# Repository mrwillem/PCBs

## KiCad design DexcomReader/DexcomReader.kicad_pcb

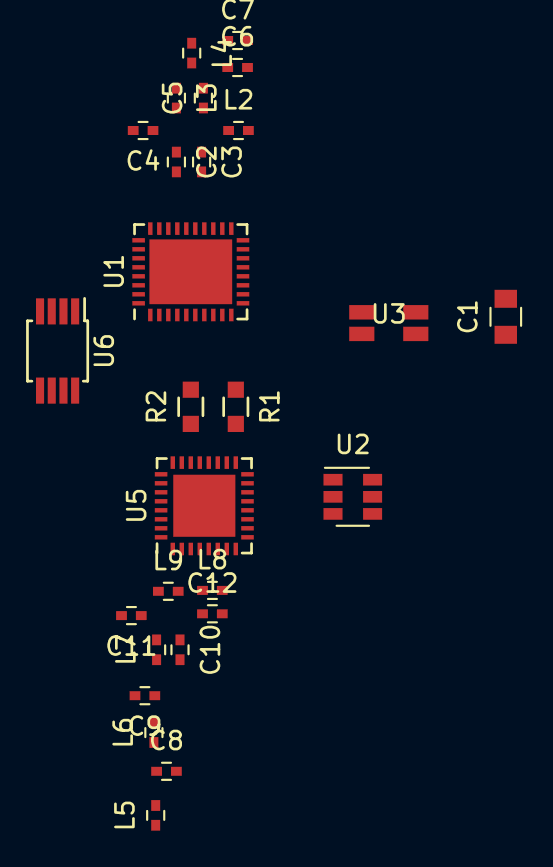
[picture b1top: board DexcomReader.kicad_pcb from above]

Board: 2 copper layers, 28 parts (1 on the bottom side), 21 nets, no tracks yet.

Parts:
C1: 100nF; C_0805
C2, C3: 100pF; C_0402
C4, C5, C8, C9, C10, C11: 1pF; C_0402
C6: 1,8pF; C_0402
C7: 1,5pF; C_0402
C12: 6,8pF; C_0402
L2, L3: 1,2nH; C_0402
L4, L5, L6: 1,2 nH; C_0402
L7: 2,7nH; C_0402
L8: 2,4nH; C_0402
L9: 6,2nH; C_0402
R1, R2: R; R_0603_HandSolder
U1: CC2511F32; QFN-36-1EP_5x6mm_Pitch0.5mm
U2: BQ21040; SOT-23-6
U3: USB-CMC-Wuerth; CMC-SMD-Wuerth
U4: TVS-ARRAY-SOT5; SOT-23-5
U5: CC2640_32PIN; QFN-32-1EP_5x5mm_Pitch0.5mm
U6: MB85RS16N; MSOP-8_3x3mm_Pitch0.65mm

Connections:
+3V3: C1.2, U6.3, U6.7, U6.8
GNDD: C1.1, C4.2, C6.2, C7.2, C8.2, C9.2, C11.2, C12.2, L2.2, R1.2, U4.2, U6.4
MEMCS: U1.35, U6.1
MISO: U1.32, U6.2
MOSI: U1.33, U6.5
unnamed: C7.1, L4.1
unnamed: C2.1, C4.1, L3.2
unnamed: C2.2, U1.24
unnamed: C3.1, C5.1, L2.1
unnamed: C3.2, U1.23
unnamed: C5.2, C6.1, L3.1, L4.2
unnamed: C8.1, L5.2, L6.1
unnamed: C10.1, L8.1, L9.2, U5.2
unnamed: C9.1, C10.2, L6.2, L7.1
unnamed: C11.1, L7.2, L9.1, U5.1
unnamed: C12.1, L8.2, U5.3
unnamed: R1.1, R2.2, U1.6
unnamed: U2.6, U4.5
SCK: U1.34, U6.6
USBDM: U1.11, U3.2, U4.4
USBDP: U1.10, U3.3, U4.3

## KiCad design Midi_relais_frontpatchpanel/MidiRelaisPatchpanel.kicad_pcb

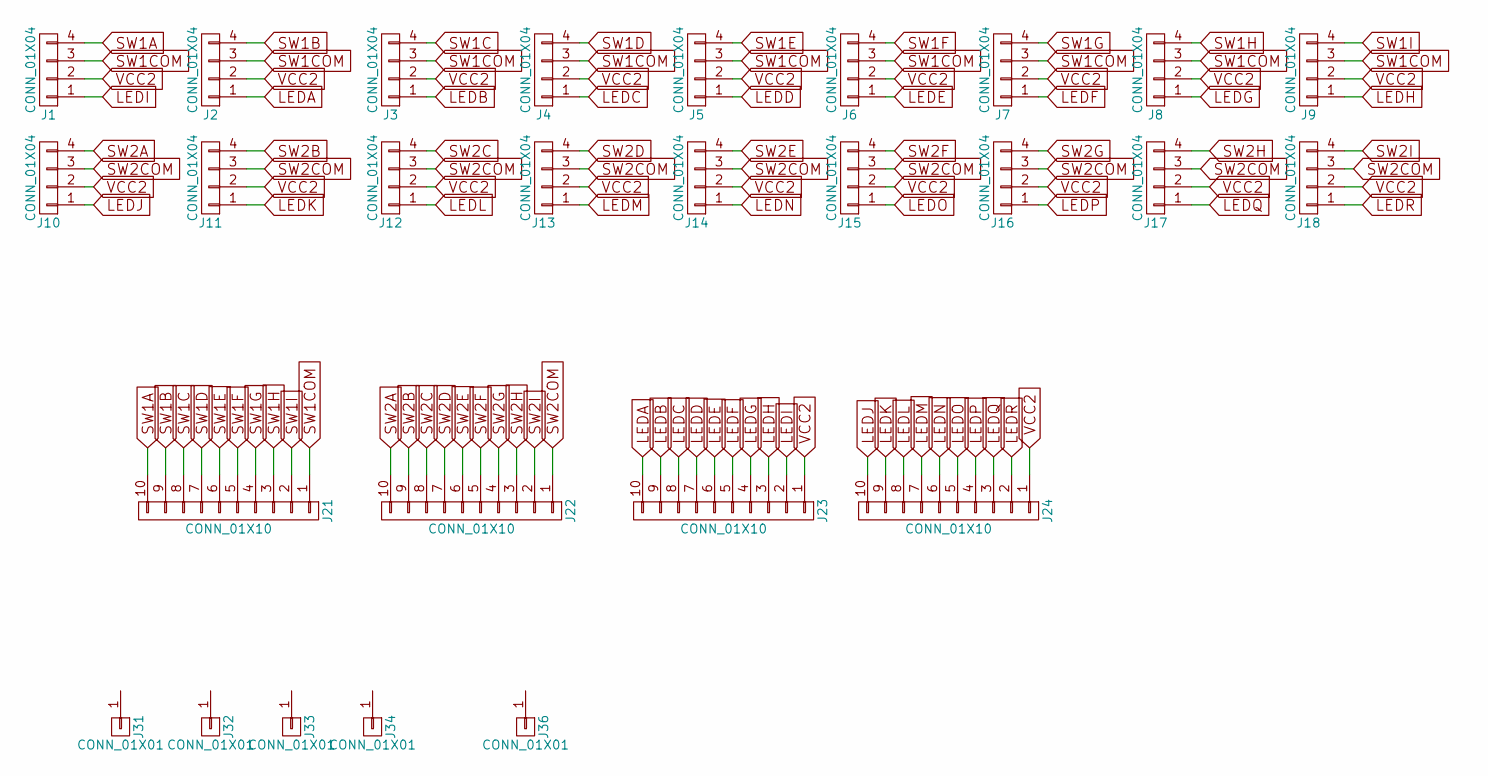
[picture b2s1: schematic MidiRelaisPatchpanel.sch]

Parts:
J1, J2, J3, J4, J5, J6, J7, J8, J9, J10, J11, J12, J13, J14, J15, J16, J17, J18: CONN_01X04; JST_ZH_1.5mm_01x04
J21, J22, J23, J24: CONN_01X10; PINHEAD1-10
J31, J32, J33, J34, J36: CONN_01X01; MountingHole_3.2mm_M3

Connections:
LEDA: J2.1, J23.10
LEDB: J3.1, J23.9
LEDC: J4.1, J23.8
LEDD: J5.1, J23.7
LEDE: J6.1, J23.6
LEDF: J7.1, J23.5
LEDG: J8.1, J23.4
LEDH: J9.1, J23.3
LEDI: J1.1, J23.2
LEDJ: J10.1, J24.10
LEDK: J11.1, J24.9
LEDL: J12.1, J24.8
LEDM: J13.1, J24.7
LEDN: J14.1, J24.6
LEDO: J15.1, J24.5
LEDP: J16.1, J24.4
LEDQ: J17.1, J24.3
LEDR: J18.1, J24.2
SW1A: J1.4, J21.10
SW1B: J2.4, J21.9
SW1C: J3.4, J21.8
SW1COM: J1.3, J2.3, J3.3, J4.3, J5.3, J6.3, J7.3, J8.3, J9.3, J21.1
SW1D: J4.4, J21.7
SW1E: J5.4, J21.6
SW1F: J6.4, J21.5
SW1G: J7.4, J21.4
SW1H: J8.4, J21.3
SW1I: J9.4, J21.2
SW2A: J10.4, J22.10
SW2B: J11.4, J22.9
SW2C: J12.4, J22.8
SW2COM: J10.3, J11.3, J12.3, J13.3, J14.3, J15.3, J16.3, J17.3, J18.3, J22.1
SW2D: J13.4, J22.7
SW2E: J14.4, J22.6
SW2F: J15.4, J22.5
SW2G: J16.4, J22.4
SW2H: J17.4, J22.3
SW2I: J18.4, J22.2
VCC2: J1.2, J2.2, J3.2, J4.2, J5.2, J6.2, J7.2, J8.2, J9.2, J10.2, J11.2, J12.2, J13.2, J14.2, J15.2, J16.2, J17.2, J18.2, J23.1, J24.1

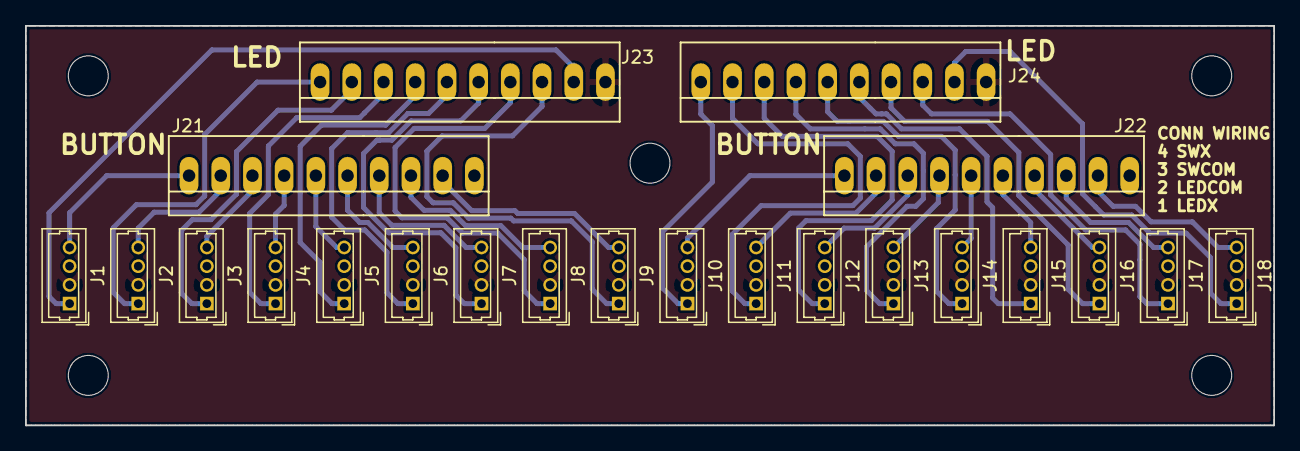
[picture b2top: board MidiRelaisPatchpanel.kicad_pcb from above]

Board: 2 copper layers, 100.0 x 32.0 mm, 27 parts (0 on the bottom side), 39 nets.

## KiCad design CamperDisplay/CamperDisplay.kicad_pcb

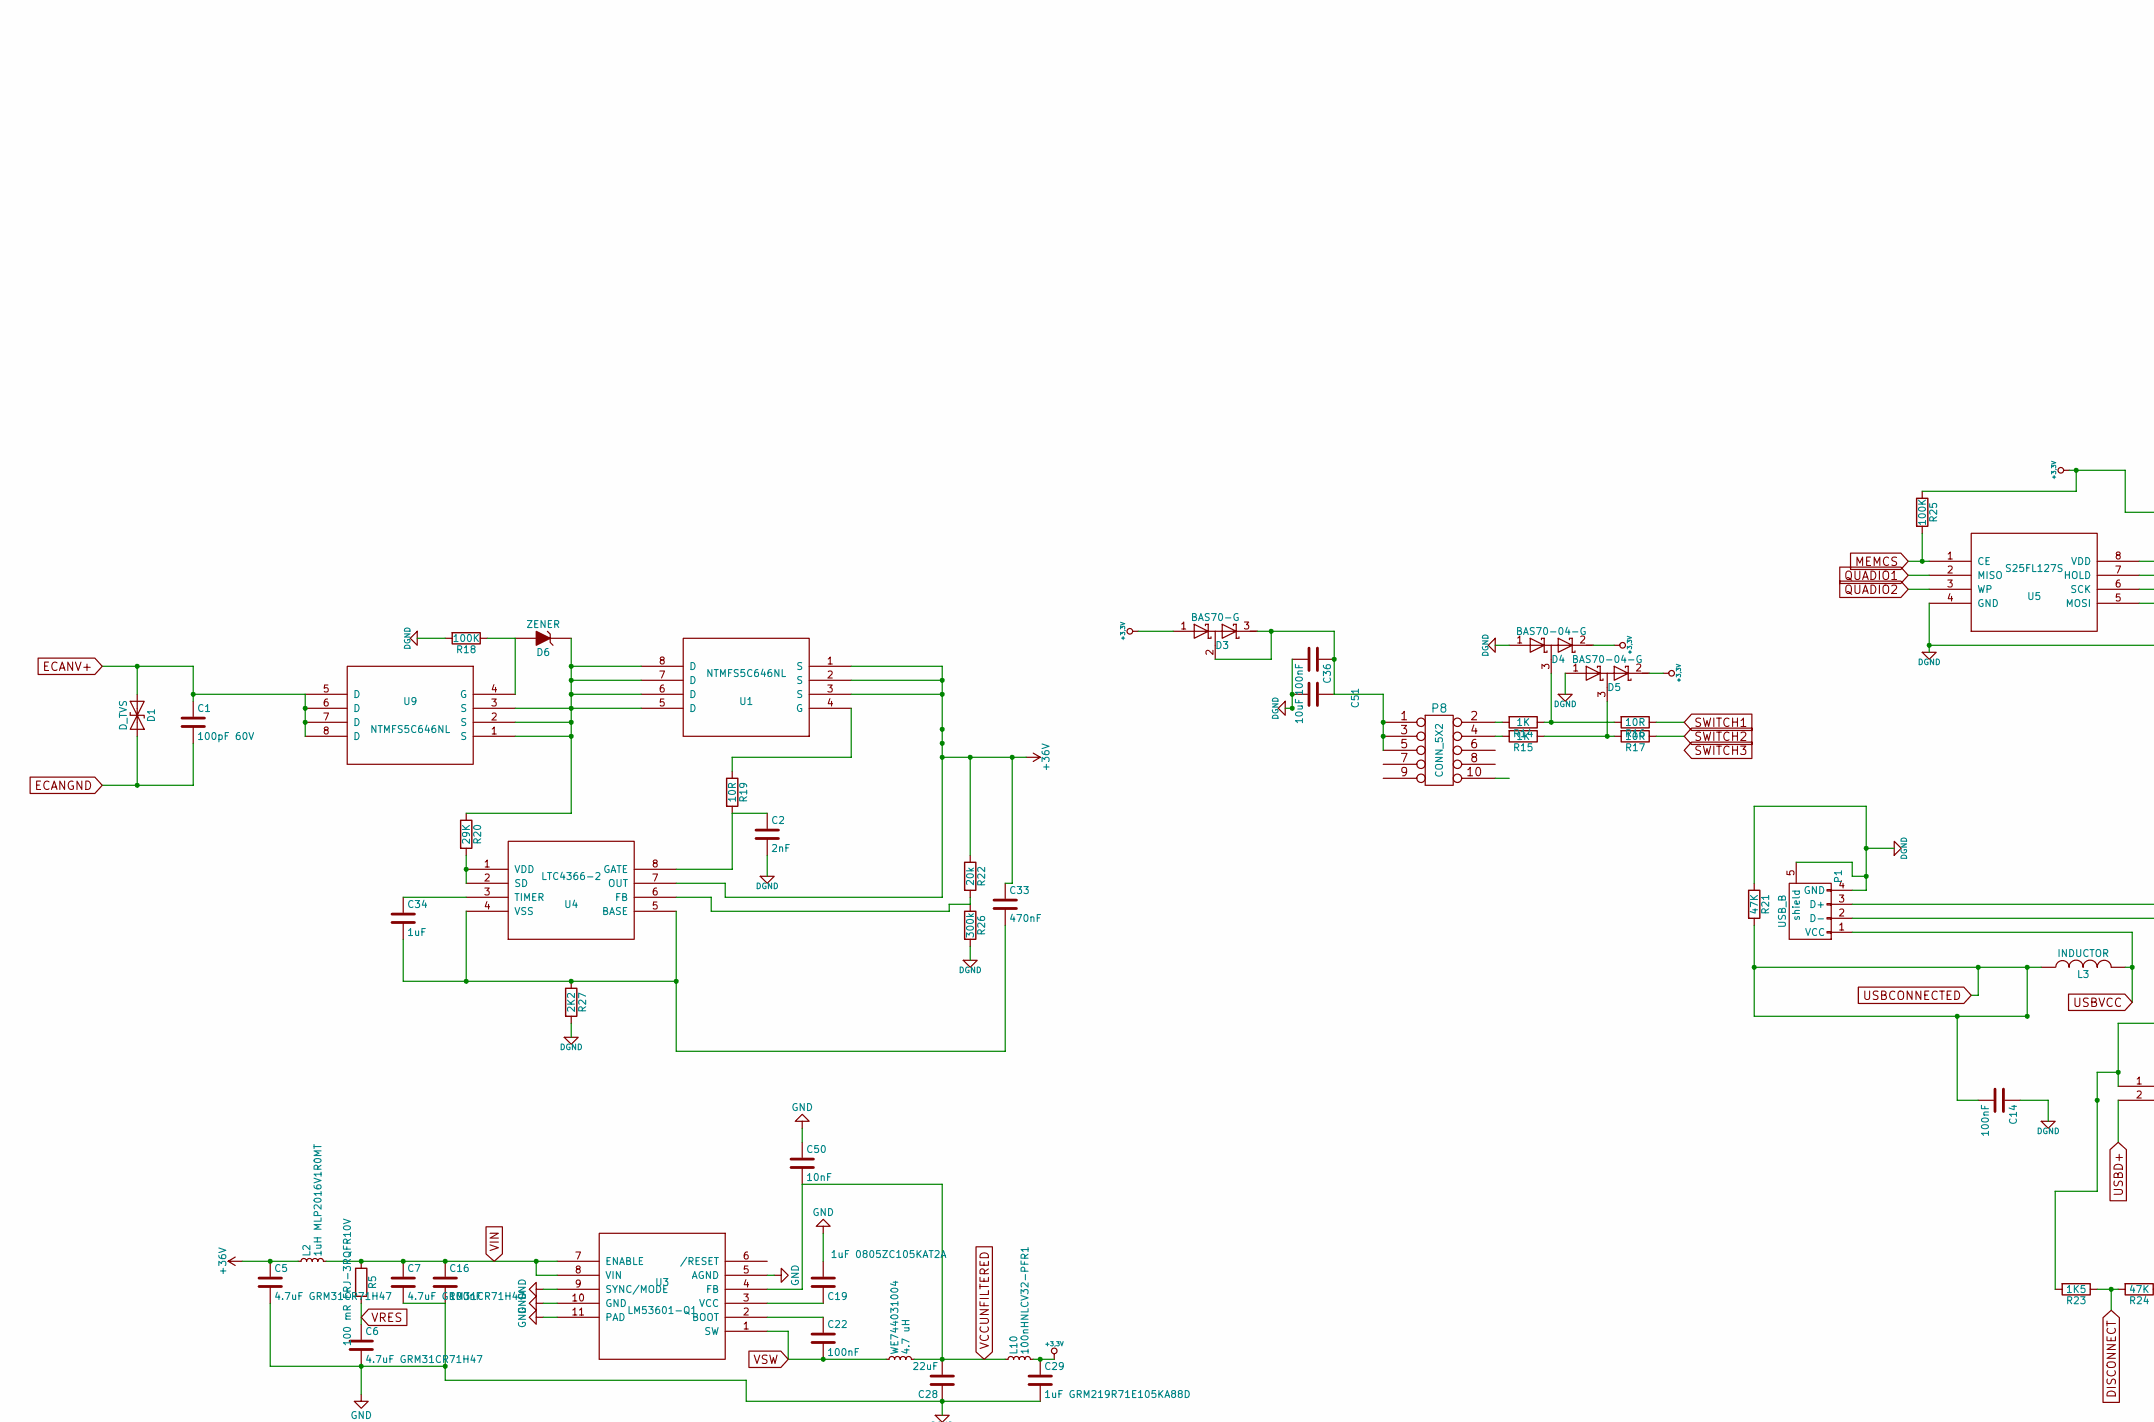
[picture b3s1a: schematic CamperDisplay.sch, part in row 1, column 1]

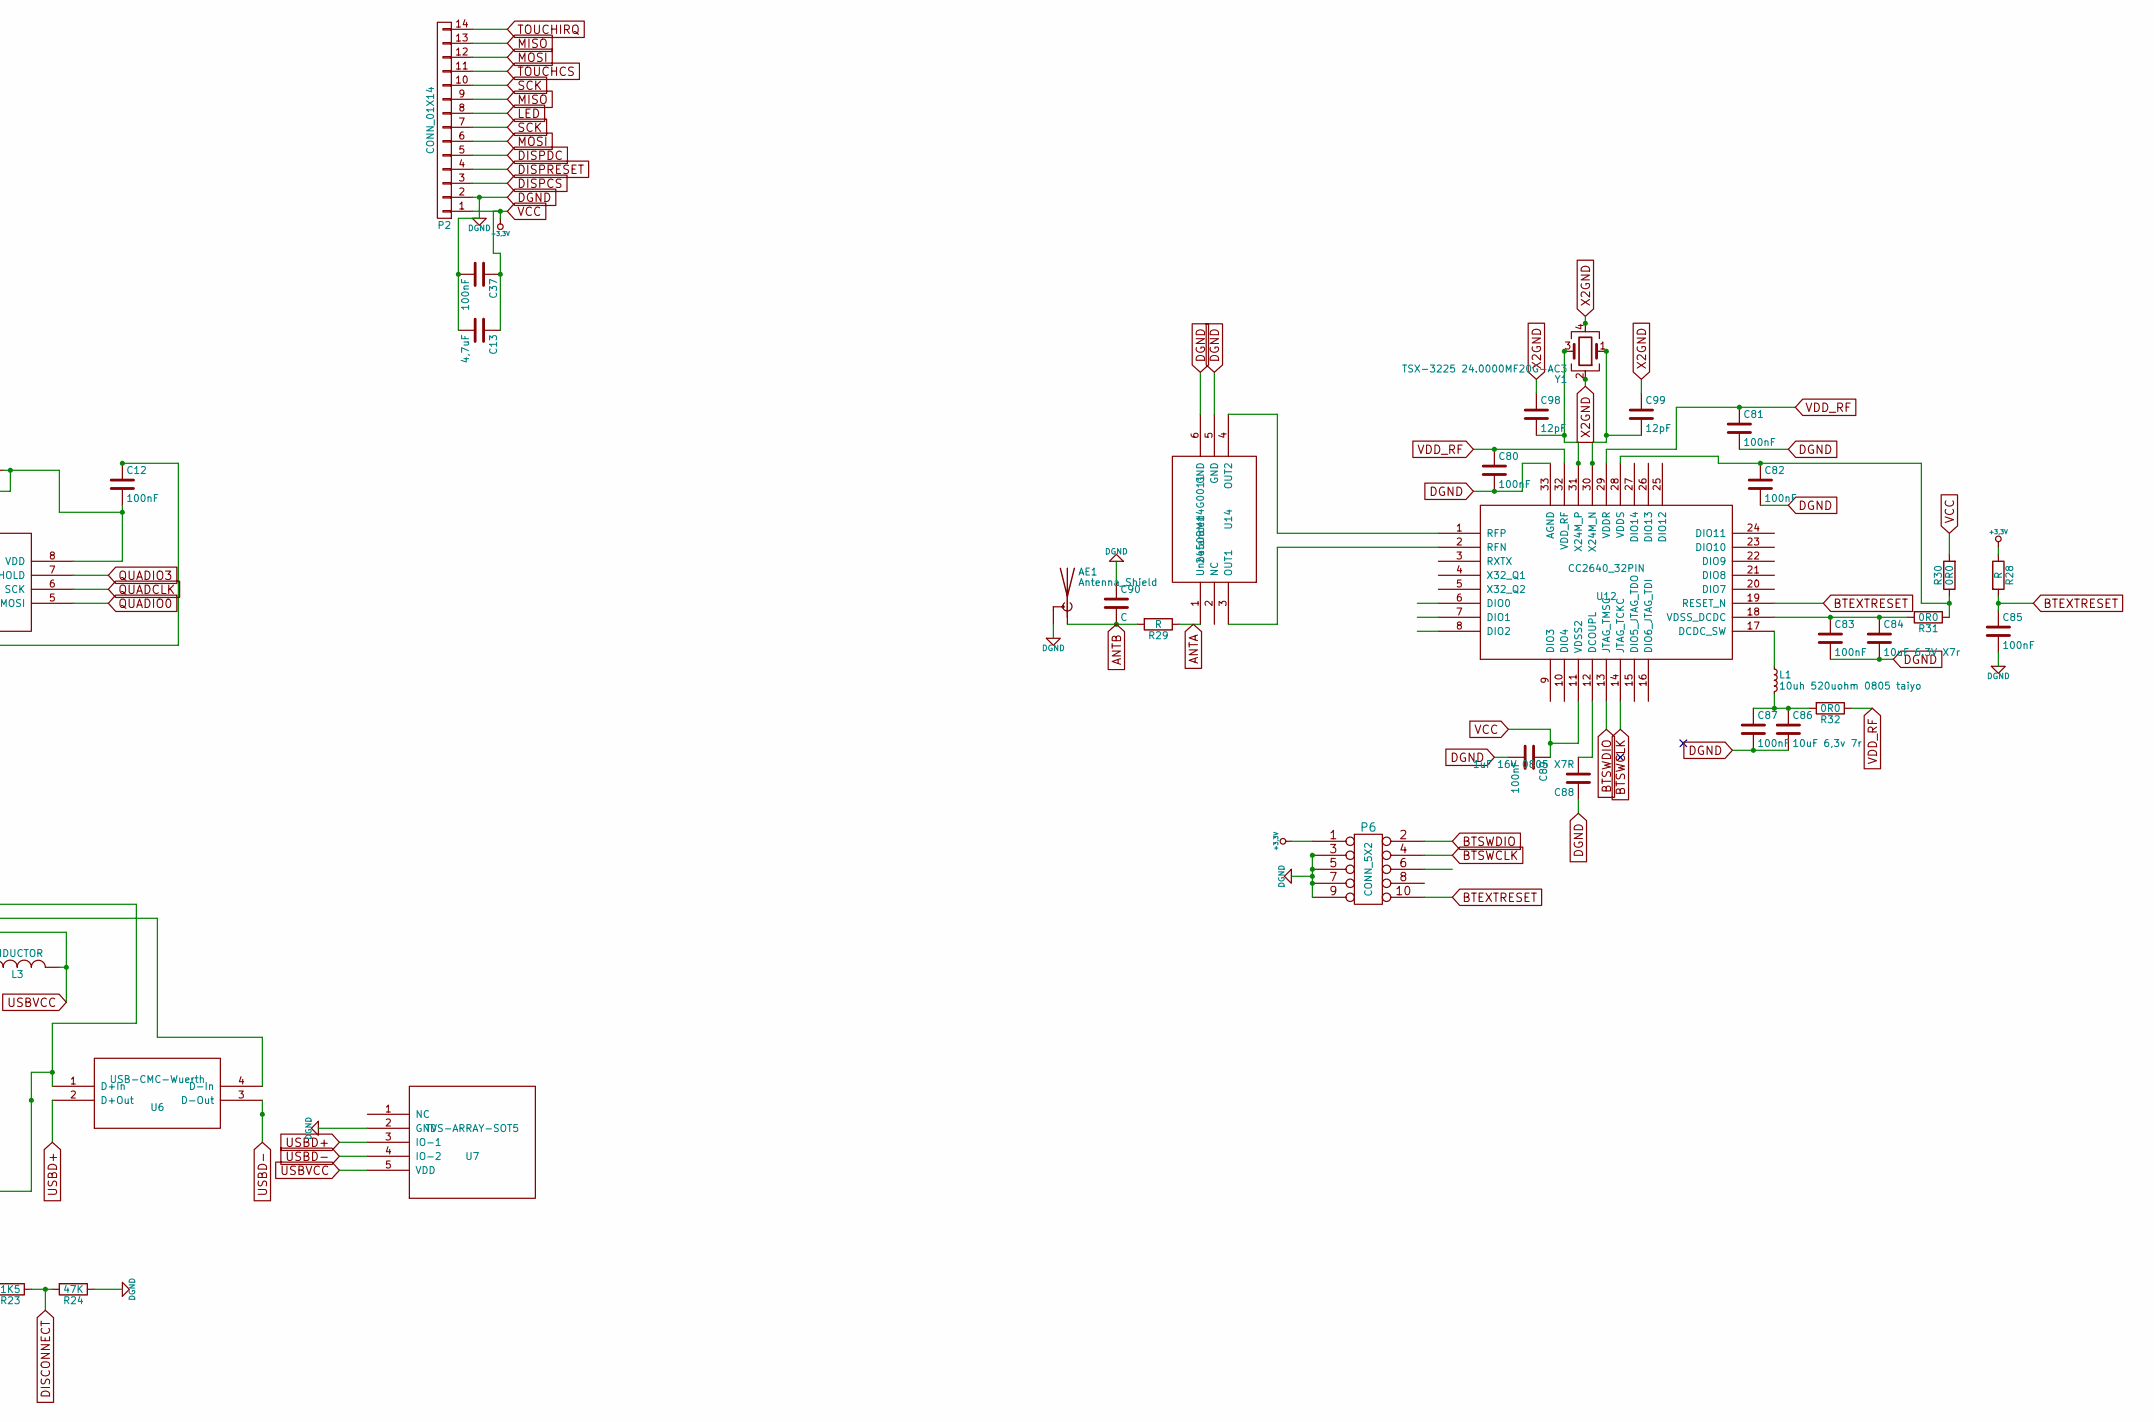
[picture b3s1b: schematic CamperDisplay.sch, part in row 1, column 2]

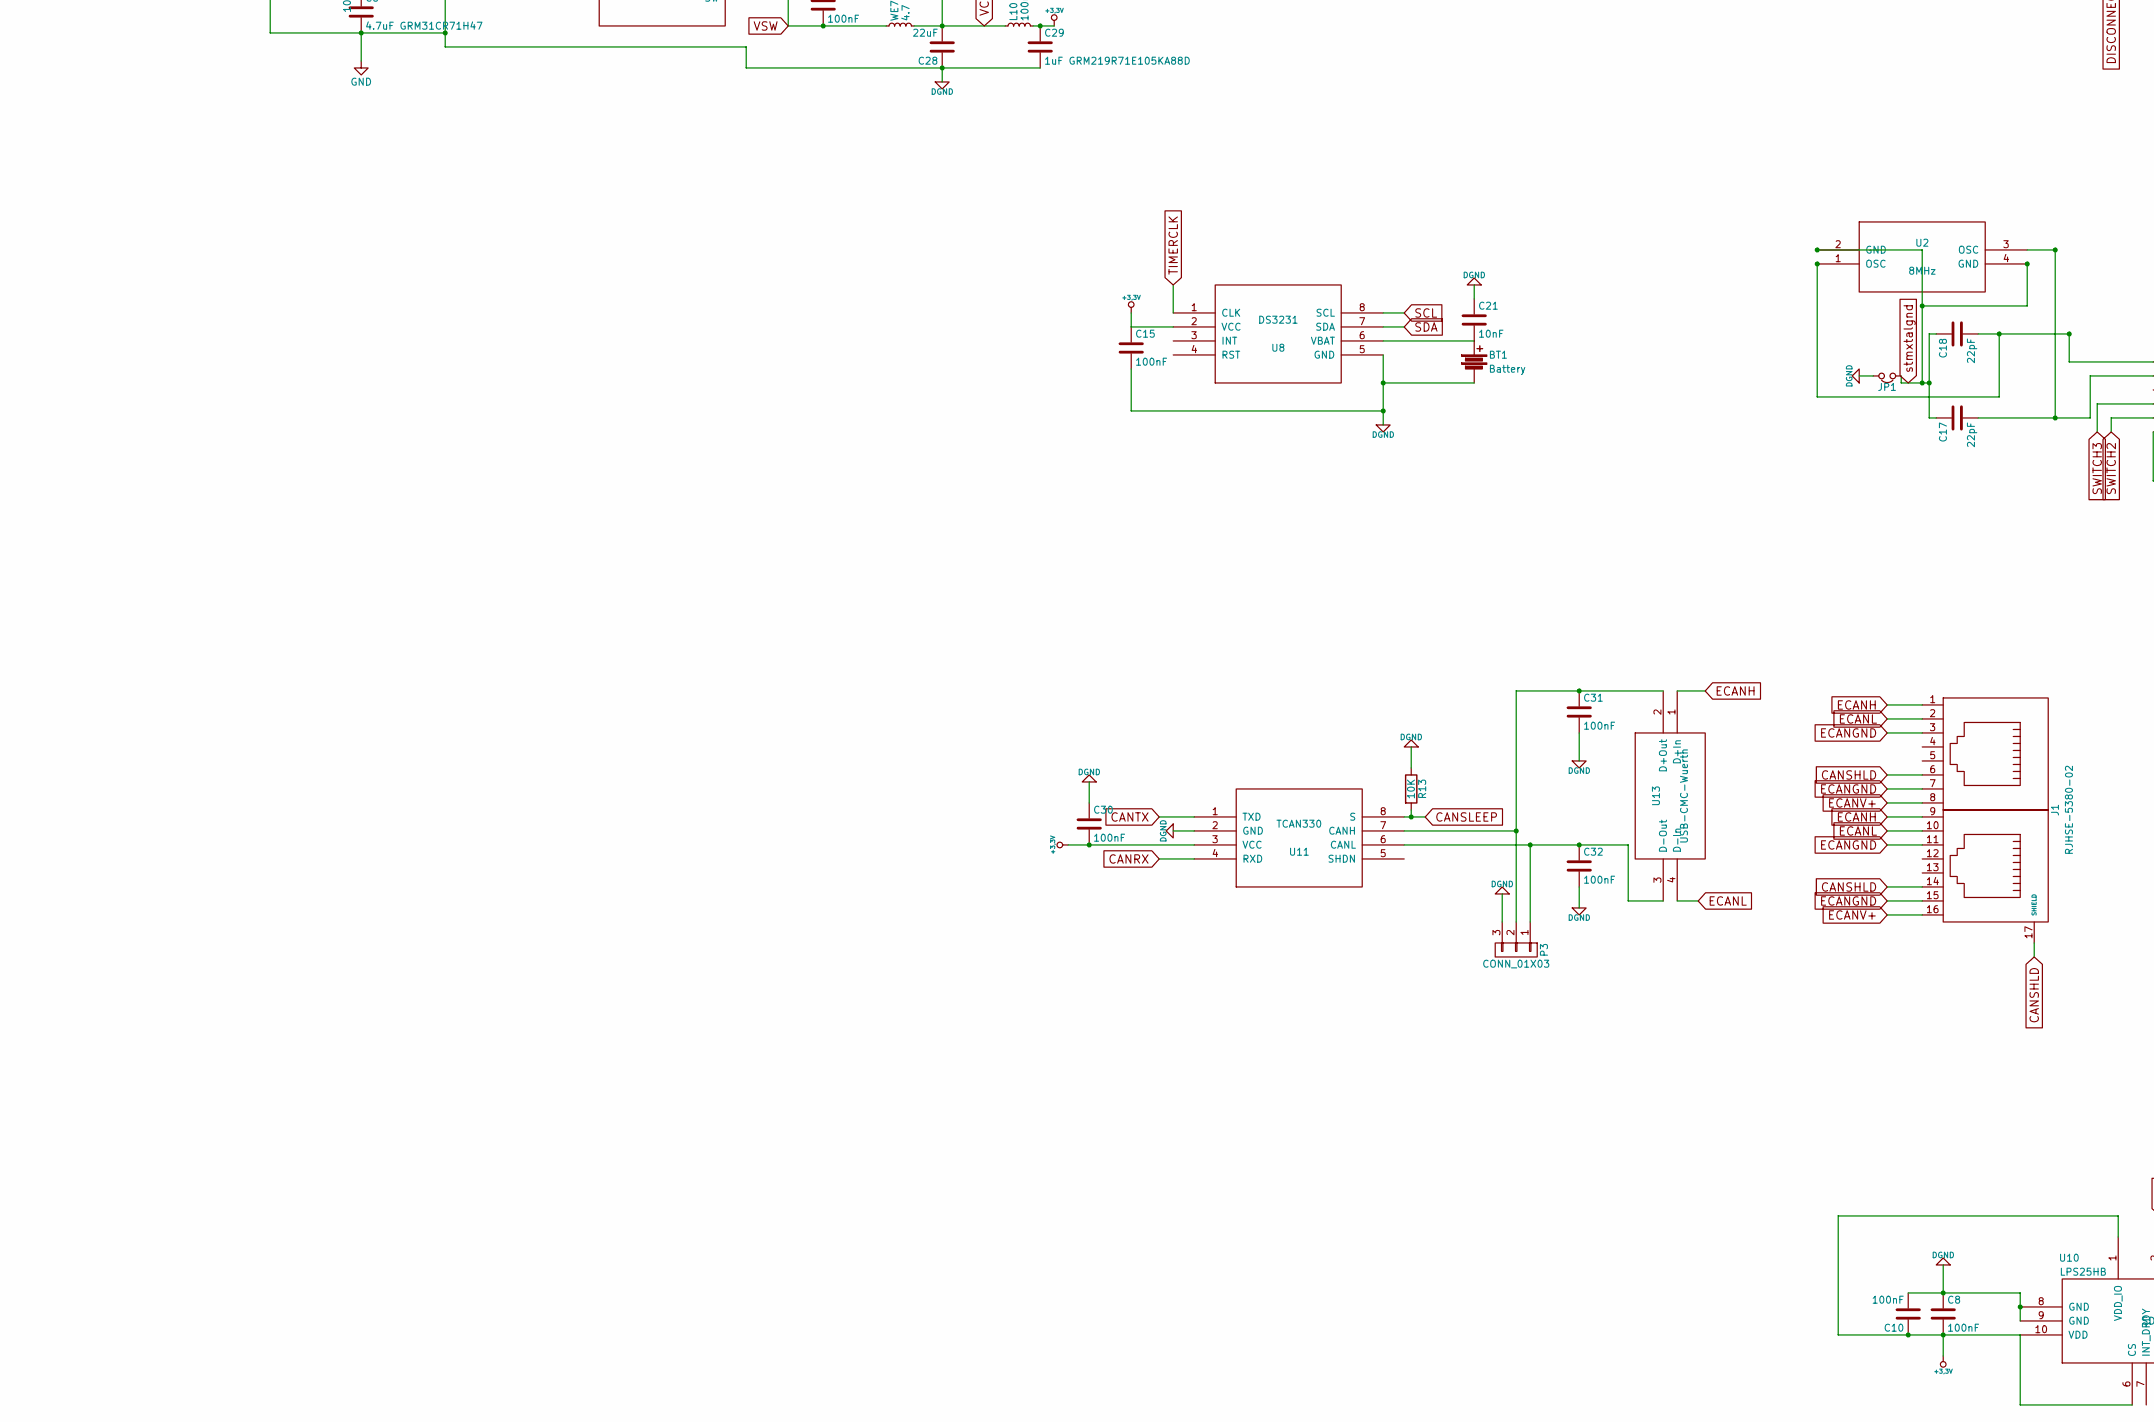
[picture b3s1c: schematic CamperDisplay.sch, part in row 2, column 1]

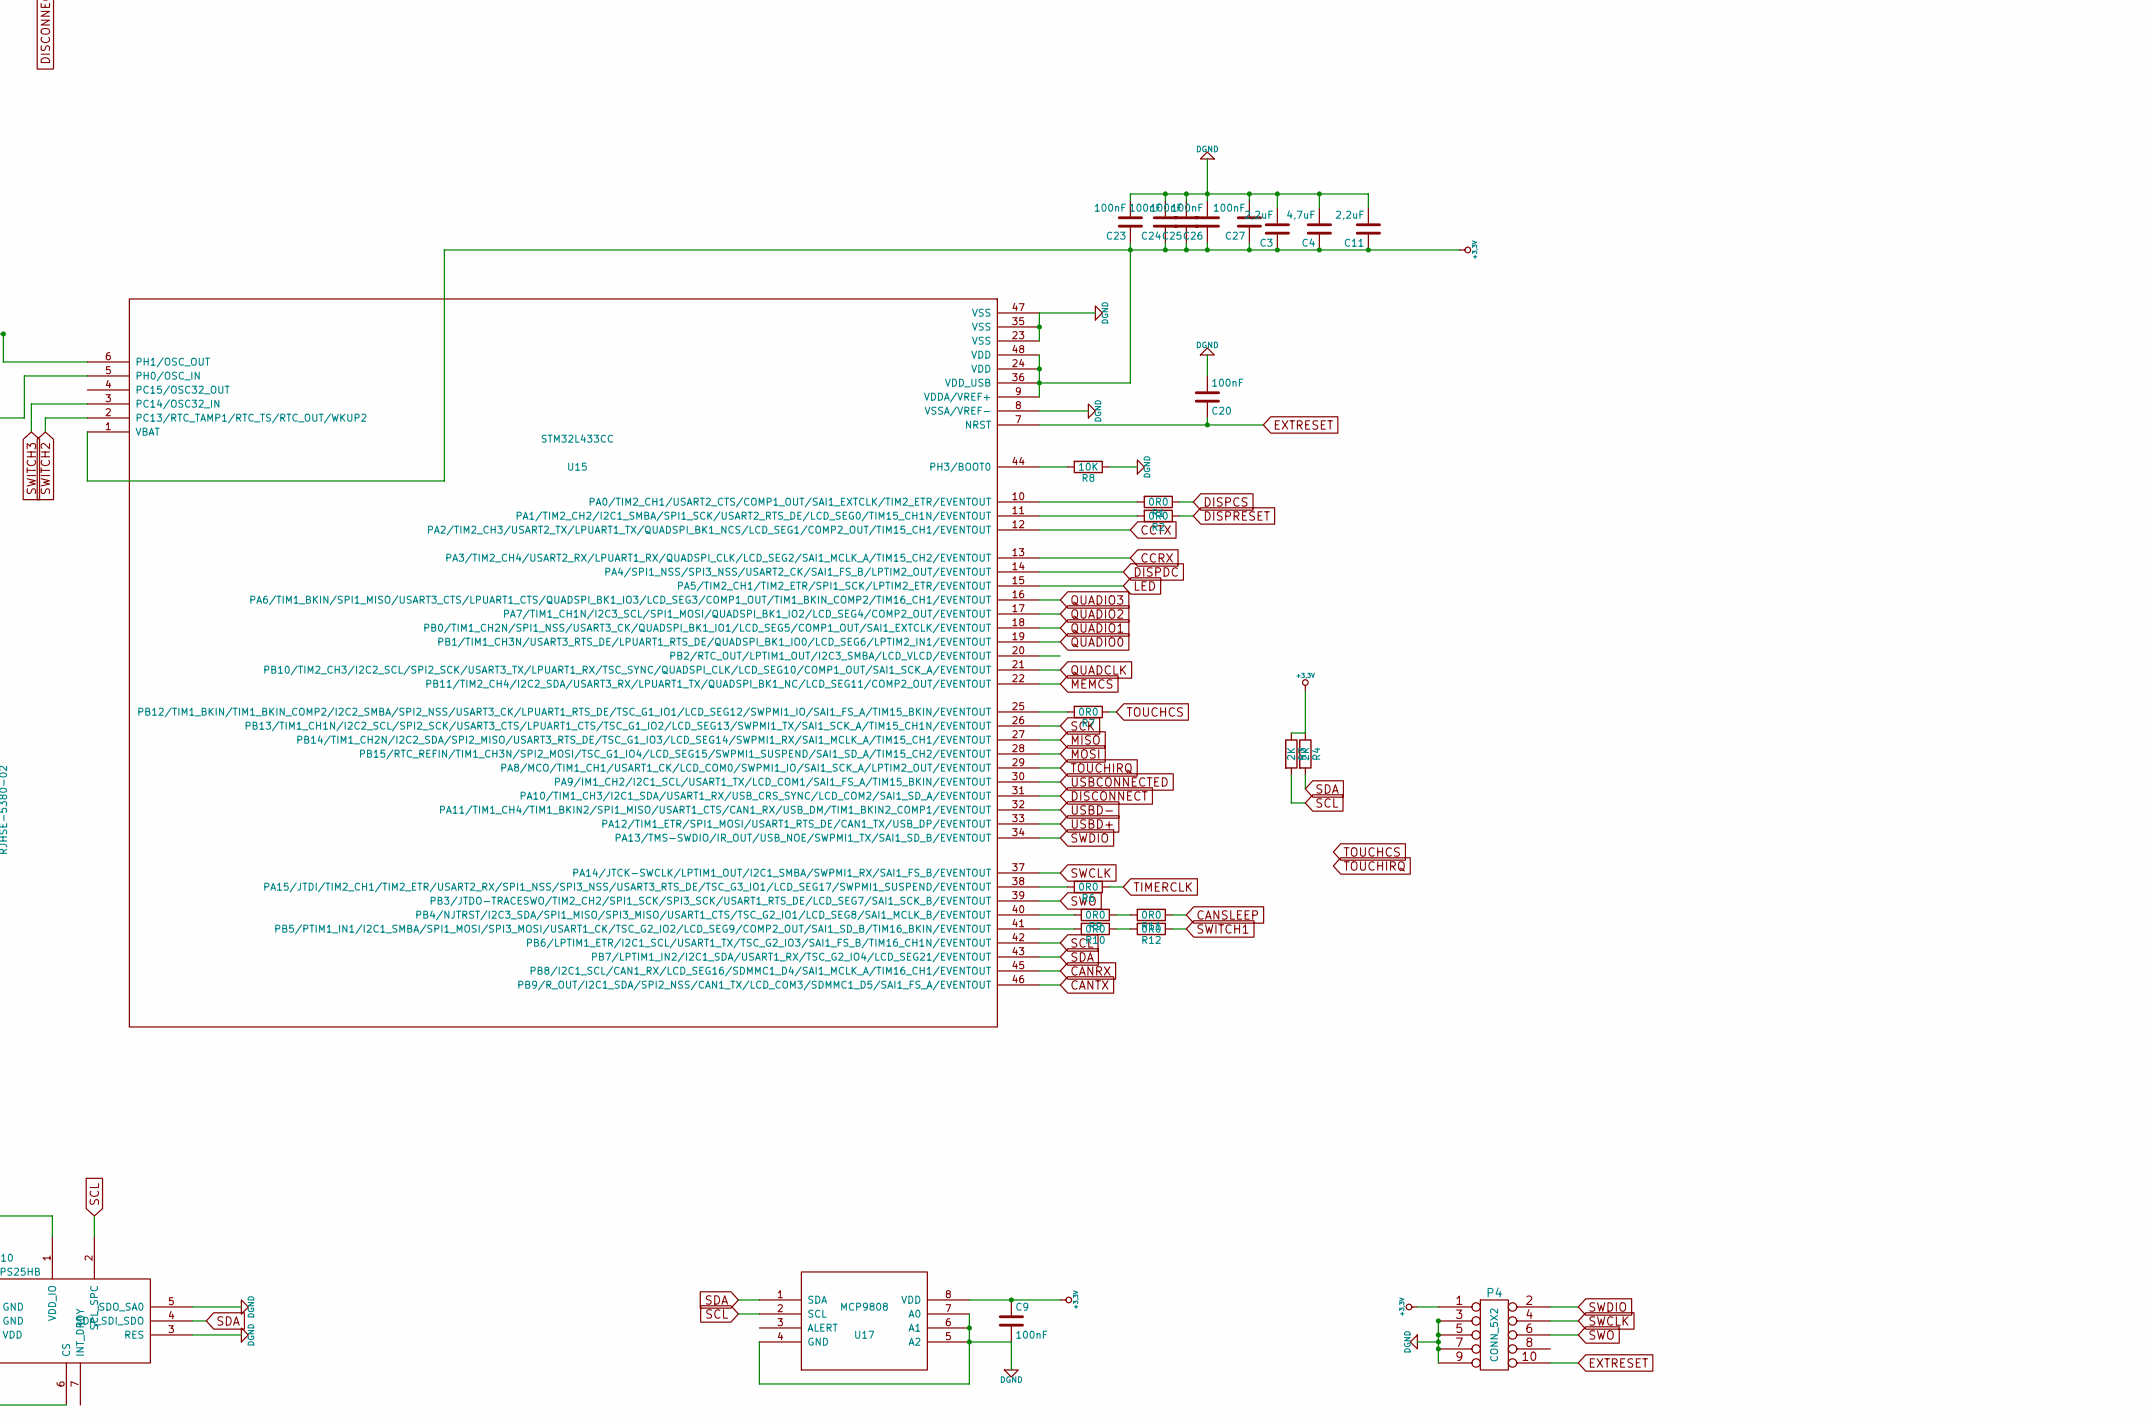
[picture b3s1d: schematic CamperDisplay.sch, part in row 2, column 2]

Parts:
AE1: Antenna_Shield; Molex_2.4GhZ_Chip_Antenna_146175
BT1: Battery; BatterieHolderCR1025_SMD
C1: 100pF 60V; C_0805
C2: 2nF; C_0805
C3: 2,2uF; C_0805
C4, C13: 4,7uF; C_1206
C5, C6, C7: 4.7uF GRM31CR71H47; C_1206
C8, C9, C10, C12, C14, C15, C16, C20, C22, C23, C24, C25, C26, C27, C30, C31, C32, C36, C37: 100nF; C_0805
C11: 2,2uF; C_1206
C17, C18: 22pF; C_0805
C19: 1uF 0805ZC105KAT2A; C_0805
C21, C50: 10nF; C_0805
C28: 22uF; C_1210
C29: 1uF GRM219R71E105KA88D; C_0805
C33: 470nF; C_0805
C34: 1uF; C_0805
C51: 10uF; C_1206
C80, C81, C82, C83, C85, C87, C89: 100nF; C_0603
C84: 10uF 6.3V X7r; C_0603
C86: 10uF 6,3v 7r; C_0603
C88: 1uF 16V 0805 X7R; C_0603
C90: C; C_0402
C98, C99: 12pF; C_0603
D1: D_TVS; D_SMB_Standard
D3: BAS70-G; SOT-23
D4, D5: BAS70-04-G; SOT-23
D6: ZENER; D_SOD-323_HandSoldering
J1: RJHSE-5380-02; RJHSE538X-02-noled
JP1: Jumper_NC_Small; NetTie-I_Connected_SMD
L1: 10uh 520uohm 0805 taiyo
L2: 1uH MLP2016V1R0MT; Choke_SMD_2016_Standard
L3: INDUCTOR; C_0805_HandSoldering
L10: 100nHNLCV32-PFR1; Choke_SMD_3225_Standard
P1: USB_B; USB_Mini-B
P2: CONN_01X14; 2.4inchQVGASPIwithTouch
P3: CONN_01X03; SOT-23
P4, P6: CONN_5X2; Pin_Header_Straight_2x05_Pitch1.27mm
P8: CONN_5X2; weidmueller_8
R1, R2, R7: 0R0; R_1206
R3, R4: 2K; R_0805_HandSolder
R5: 100 mR ERJ-3RQFR10V; R_0805
R6, R9, R10, R11, R12, R30, R31, R32: 0R0; R_0805_HandSolder
R8, R13: 10K; R_0805_HandSolder
R14, R15: 1K; R_0805_HandSolder
R16, R17, R19: 10R; R_0805_HandSolder
R18, R25: 100K; R_0805_HandSolder
R20: 29K; R_0805_HandSolder
R21, R24: 47K; R_0603_HandSolder
R22: 20k; R_0805_HandSolder
R23: 1K5; R_0603_HandSolder
R26: 300k; R_0805_HandSolder
R27: 2K2; R_0805_HandSolder
R28: R; R_0805_HandSolder
R29: R; R_0402
U1, U9: NTMFS5C646NL; PowerPack1212-8S_Pitch0.65mm
U2: 8MHz; Crystal_SMD_EuroQuartz_MT-4pin_3.2x2.5mm_hand
U3: LM53601-Q1; VSON10_Thermal_Pad
U4: LTC4366-2; SOT23-8
U5: S25FL127S; SOIJ-8_5.3x5.3mm_Pitch1.27mm
U6, U13: USB-CMC-Wuerth; CMC-SMD-Wuerth
U7: TVS-ARRAY-SOT5; SOT-23-5
U8: DS3231; SOIC-8_3.9x4.9mm_Pitch1.27mm
U10: LPS25HB; HLGA-10_2x2mm_Pitch0.5mm
U11: TCAN330; SOIC-8_3.9x4.9mm_Pitch1.27mm
U12: CC2640_32PIN; QFN-32-1EP_5x5mm_Pitch0.5mm_HandSolder
U14: 2450BM14G0011
U15: STM32L433CC; LQFP-48_7x7mm_Pitch0.5mm
U17: MCP9808; MSOP-8_3x3mm_Pitch0.65mm
WE744031004: 4.7 uH; Choke_SMD_4.3x4.3_H3
Y1: TSX-3225 24.0000MF20G-AC3; Crystal_SMD_EuroQuartz_MT-4pin_3.2x2.5mm_hand

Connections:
+36V: C5.1, C33.1, L2.1, R22.1, U1.1 (S), U1.2 (S), U1.3 (S), U4.7 (OUT)
ANTA: R29.1, U14.1 (Unbalanced)
ANTB: AE1.1 (A), C90.2, R29.2
BTEXTRESET: C85.1, P6.10, R28.2, U12.19 (RESET_N)
BTSWCLK: P6.4, U12.14 (JTAG_TCKC)
BTSWDIO: P6.2, U12.13 (JTAG_TMSC)
CANRX: U11.4 (RXD), U15.45 (PB8/I2C1_SCL/CAN1_RX/LCD_SEG16/SDMMC1_D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)
CANSHLD: J1.6, J1.14, J1.17 (SHIELD)
CANSLEEP: R11.1, R13.2, U11.8 (S)
CANTX: U11.1 (TXD), U15.46 (PB9/R_OUT/I2C1_SDA/SPI2_NSS/CAN1_TX/LCD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)
DGND: AE1.2 (Shield), BT1.2, C2.2, C3.2, C4.2, C5.2, C6.2, C7.2, C8.1, C9.2, C10.2, C11.2, C12.1, C13.2, C14.1, C15.2, C16.2, C19.2, C20.2, C21.1, C23.2, C24.2, C25.2, C26.2, C27.2, C28.1, C29.2, C30.1, C31.2, C32.2, C36.2, C37.2, C50.1, C51.2, C80.2, C81.2, C82.2, C83.2, C84.2, C85.2, C86.2, C87.2, C88.1, C89.2, C90.1, D4.1 (A), D5.1 (A), JP1.1, P1.4 (GND), P1.5 (shield), P2.2, P3.3, P4.3, P4.5, P4.7, P4.9, P6.3, P6.5, P6.7, P6.9, R8.1, R13.1, R18.2, R21.1, R24.1, R26.2, R27.2, U3.5 (AGND), U3.9 (SYNC/MODE), U3.10 (GND), U3.11 (PAD), U5.4 (GND), U7.2 (GND), U8.5 (GND), U10.3 (RES), U10.5 (SDO_SA0), U10.8 (GND), U10.9 (GND), U11.2 (GND), U12.33 (AGND), U14.5 (GND), U14.6 (GND), U15.8 (VSSA/VREF-), U15.23 (VSS), U15.35 (VSS), U15.47 (VSS), U17.4 (GND), U17.5 (A2), U17.6 (A1), U17.7 (A0)
DISCONNECT: R23.1, R24.2, U15.31 (PA10/TIM1_CH3/I2C1_SDA/USART1_RX/USB_CR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)
DISPCS: P2.3, R1.1
DISPDC: P2.5, U15.14 (PA4/SPI1_NSS/SPI3_NSS/USART2_CK/SAI1_FS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)
DISPRESET: P2.4, R2.1
ECANGND: C1.2, D1.2 (A2), J1.3, J1.7, J1.11, J1.15
ECANH: J1.1, J1.9, U13.1 (D+In)
ECANL: J1.2, J1.10, U13.4 (D-In)
ECANV+: C1.1, D1.1 (A1), J1.8, J1.16, U9.5 (D), U9.6 (D), U9.7 (D), U9.8 (D)
EXTRESET: C20.1, P4.10, U15.7 (NRST)
LED: P2.8, U15.15 (PA5/TIM2_CH1/TIM2_ETR/SPI1_SCK/LPTIM2_E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)
MEMCS: R25.2, U5.1 (CE), U15.22 (PB11/TIM2_CH4/I2C2_SDA/USART3_RX/LPUART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)
MISO: P2.9, P2.13, U15.27 (PB14/TIM1_CH2N/I2C2_SDA/SPI2_MISO/USART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)
MOSI: P2.6, P2.12, U15.28 (PB15/RTC_REFIN/TIM1_CH3N/SPI2_MOSI/TSC_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)
unnamed: BT1.1, C21.2, U8.6 (VBAT)
unnamed: C2.1, R19.2, U4.8 (GATE)
unnamed: C17.2, U2.3 (OSC), U15.5 (PH0/OSC_IN)
unnamed: C18.2, U2.1 (OSC), U15.6 (PH1/OSC_OUT)
unnamed: C19.1, U3.3 (VCC)
unnamed: C22.1, U3.2 (BOOT)
unnamed: C31.1, P3.2, U11.7 (CANH), U13.2 (D+Out)
unnamed: C32.1, P3.1, U11.6 (CANL), U13.3 (D-Out)
unnamed: C33.2, C34.2, R27.1, U4.4 (VSS), U4.5 (BASE)
unnamed: C34.1, U4.3 (TIMER)
unnamed: C36.1, C51.1, D3.2 (common), D3.3 (K), P8.1, P8.3, P8.5
unnamed: C82.1, R30.1, R31.1, U12.28 (VDDS)
unnamed: C83.1, C84.1, R31.2, U12.18 (VDSS_DCDC)
unnamed: C86.1, C87.1, L1.2, R32.2
unnamed: C88.2, U12.12 (DCOUPL)
unnamed: C98.2, U12.31 (X24M_P), Y1.3
unnamed: C99.2, U12.30 (X24M_N), Y1.1
unnamed: D4.3 (common), R14.1, R16.2
unnamed: D5.3 (common), R15.1, R17.2
unnamed: D6.1 (K), R20.1, U1.5 (D), U1.6 (D), U1.7 (D), U1.8 (D), U9.1 (S), U9.2 (S), U9.3 (S)
unnamed: D6.2 (A), R18.1, U9.4 (G)
unnamed: L1.1, U12.17 (DCDC_SW)
unnamed: P1.2 (D-), U6.4 (D-In)
unnamed: P1.3 (D+), R23.2, U6.1 (D+In)
unnamed: P8.2, R14.2
unnamed: P8.4, R15.2
unnamed: R1.2, U15.10 (PA0/TIM2_CH1/USART2_CTS/COMP1_OUT/SAI1_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)
unnamed: R2.2, U15.11 (PA1/TIM2_CH2/I2C1_SMBA/SPI1_SCK/USART2_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)
unnamed: R6.2, U15.38 (PA15/JTDI/TIM2_CH1/TIM2_ETR/USART2_RX/S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)
unnamed: R7.2, U15.25 (PB12/TIM1_BKIN/TIM1_BKIN_COMP2/I2C2_SMB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)
unnamed: R8.2, U15.44 (PH3/BOOT0)
unnamed: R9.2, U15.40 (PB4/NJTRST/I2C3_SDA/SPI1_MISO/SPI3_MISO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)
unnamed: R10.1, R12.2
unnamed: R10.2, U15.41 (PB5/PTIM1_IN1/I2C1_SMBA/SPI1_MOSI/SPI3_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)
unnamed: R9.1, R11.2
unnamed: R19.1, U1.4 (G)
unnamed: R20.2, U4.1 (VDD), U4.2 (SD)
unnamed: R22.2, R26.1, U4.6 (FB)
unnamed: U12.1 (RFP), U14.4 (OUT2)
unnamed: U12.2 (RFN), U14.3 (OUT1)
QUADCLK: U5.6 (SCK), U15.21 (PB10/TIM2_CH3/I2C2_SCL/SPI2_SCK/USART3_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)
QUADIO0: U5.5 (MOSI), U15.19 (PB1/TIM1_CH3N/USART3_RTS_DE/LPUART1_RTS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)
QUADIO1: U5.2 (MISO), U15.18 (PB0/TIM1_CH2N/SPI1_NSS/USART3_CK/QUADSP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)
QUADIO2: U5.3 (WP), U15.17 (PA7/TIM1_CH1N/I2C3_SCL/SPI1_MOSI/QUADSP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)
QUADIO3: U5.7 (HOLD), U15.16 (PA6/TIM1_BKIN/SPI1_MISO/USART3_CTS/LPUA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)
SCK: P2.7, P2.10, U15.26 (PB13/TIM1_CH1N/I2C2_SCL/SPI2_SCK/USART3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)
SCL: R3.2, U8.8 (SCL), U10.2 (SCL_SPC), U15.42 (PB6/LPTIM1_ETR/I2C1_SCL/USART1_TX/TSC_G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), U17.2 (SCL)
SDA: R4.2, U8.7 (SDA), U10.4 (SDA_SDI_SDO), U15.43 (PB7/LPTIM1_IN2/I2C1_SDA/USART1_RX/TSC_G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), U17.1 (SDA)
SWCLK: P4.4, U15.37 (PA14/JTCK-SWCLK/LPTIM1_OUT/I2C1_SMBA/SW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)
SWDIO: P4.2, U15.34 (PA13/TMS-SWDIO/IR_OUT/USB_NOE/SWPMI1_TX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)
SWITCH1: R12.1, R16.1
SWITCH2: R17.1, U15.2 (PC13/RTC_TAMP1/RTC_TS/RTC_OUT/WKUP2)
SWO: P4.6, U15.39 (PB3/JTDO-TRACESWO/TIM2_CH2/SPI1_SCK/SPI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)
TIMERCLK: R6.1, U8.1 (CLK)
TOUCHCS: P2.11, R7.1
TOUCHIRQ: P2.14, U15.29 (PA8/MCO/TIM1_CH1/USART1_CK/LCD_COM0/SWP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)
USBCONNECTED: C14.2, L3.1, R21.2, U15.30 (PA9/IM1_CH2/I2C1_SCL/USART1_TX/LCD_COM1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)
USBD+: U6.2 (D+Out), U7.3 (IO-1), U15.33 (PA12/TIM1_ETR/SPI1_MOSI/USART1_RTS_DE/C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)
USBD-: U6.3 (D-Out), U7.4 (IO-2), U15.32 (PA11/TIM1_CH4/TIM1_BKIN2/SPI1_MISO/USAR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)
USBVCC: L3.2, P1.1 (VCC), U7.5 (VDD)
VCC: C3.1, C4.1, C8.2, C9.1, C10.1, C11.1, C12.2, C13.1, C15.1, C23.1, C24.1, C25.1, C26.1, C27.1, C29.1, C30.2, C37.1, C89.1, D3.1 (A), D4.2 (K), D5.2 (K), L10.2, P2.1, P4.1, P6.1, R3.1, R4.1, R25.1, R28.1, R30.2, U5.8 (VDD), U8.2 (VCC), U10.1 (VDD_IO), U10.6 (CS), U10.10 (VDD), U11.3 (VCC), U12.11 (VDSS2), U15.1 (VBAT), U15.9 (VDDA/VREF+), U15.24 (VDD), U15.36 (VDD_USB), U15.48 (VDD), U17.8 (VDD)
VCCUNFILTERED: C28.2, C50.2, L10.1, U3.4 (FB), WE744031004.2
VDD_RF: C80.1, C81.1, R32.1, U12.29 (VDDR), U12.32 (VDD_RF)
VIN: C7.1, C16.1, L2.2, R5.1, U3.7 (ENABLE), U3.8 (VIN)
VRES: C6.1, R5.2
VSW: C22.2, U3.1 (SW), WE744031004.1
X2GND: C98.1, C99.1, Y1.2, Y1.4
stmxtalgnd: C17.1, C18.1, JP1.2, U2.2 (GND), U2.4 (GND)
